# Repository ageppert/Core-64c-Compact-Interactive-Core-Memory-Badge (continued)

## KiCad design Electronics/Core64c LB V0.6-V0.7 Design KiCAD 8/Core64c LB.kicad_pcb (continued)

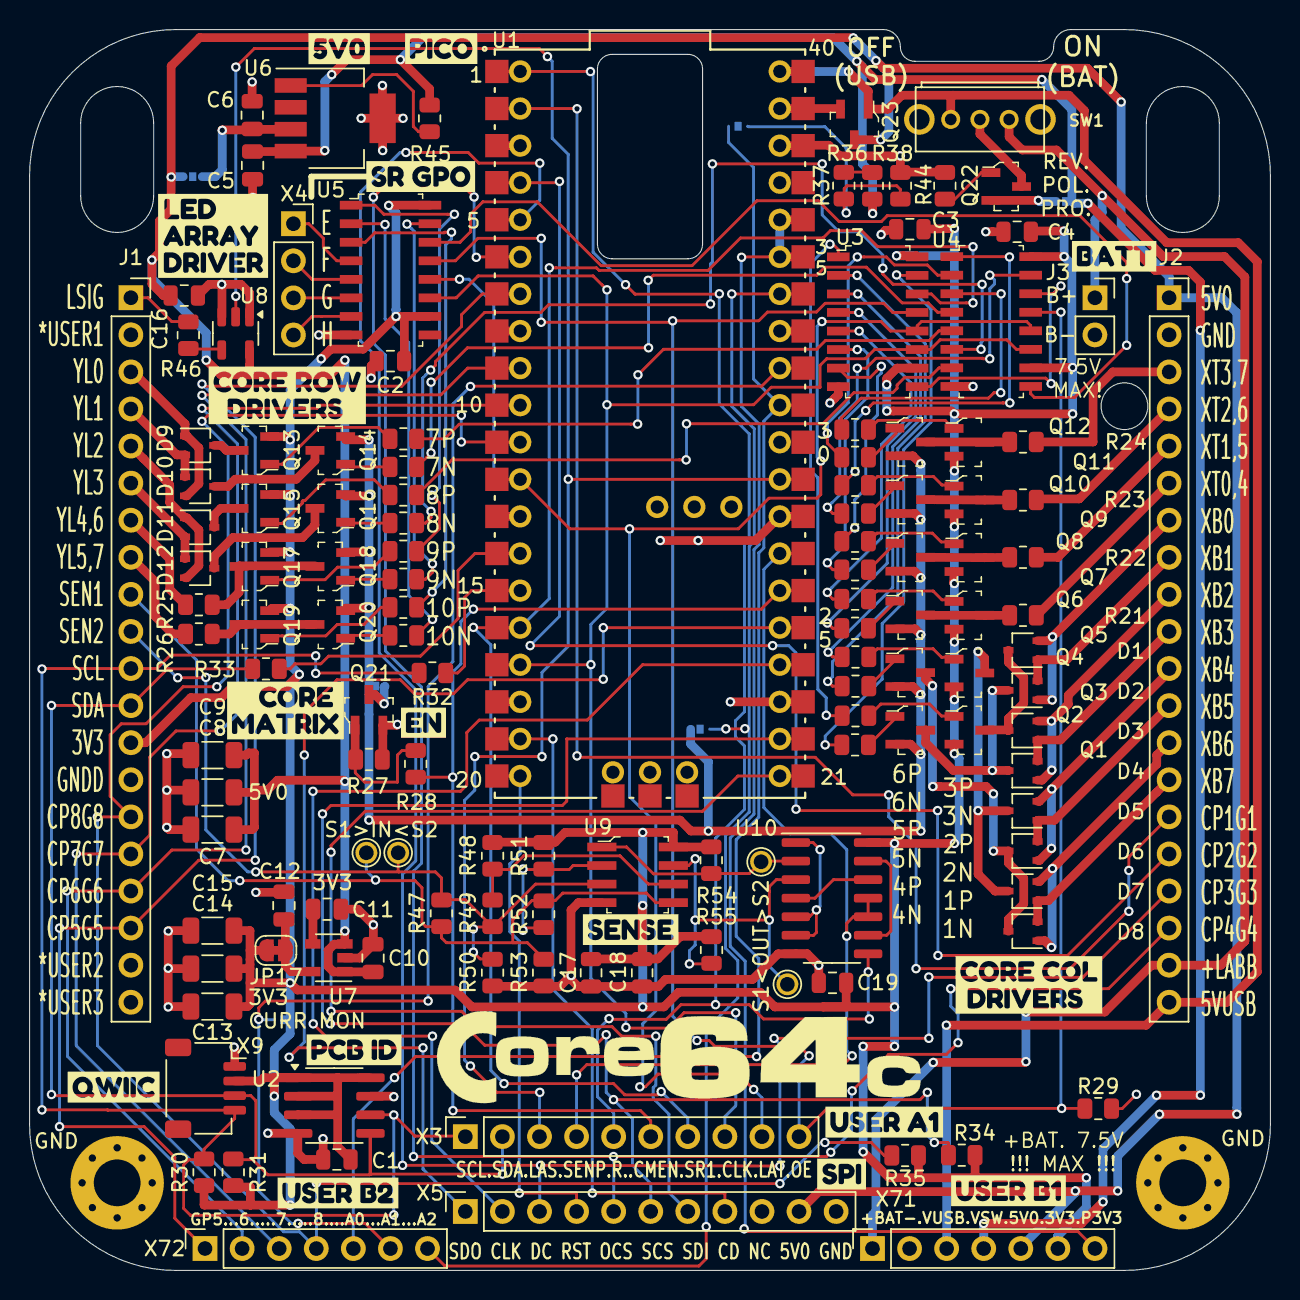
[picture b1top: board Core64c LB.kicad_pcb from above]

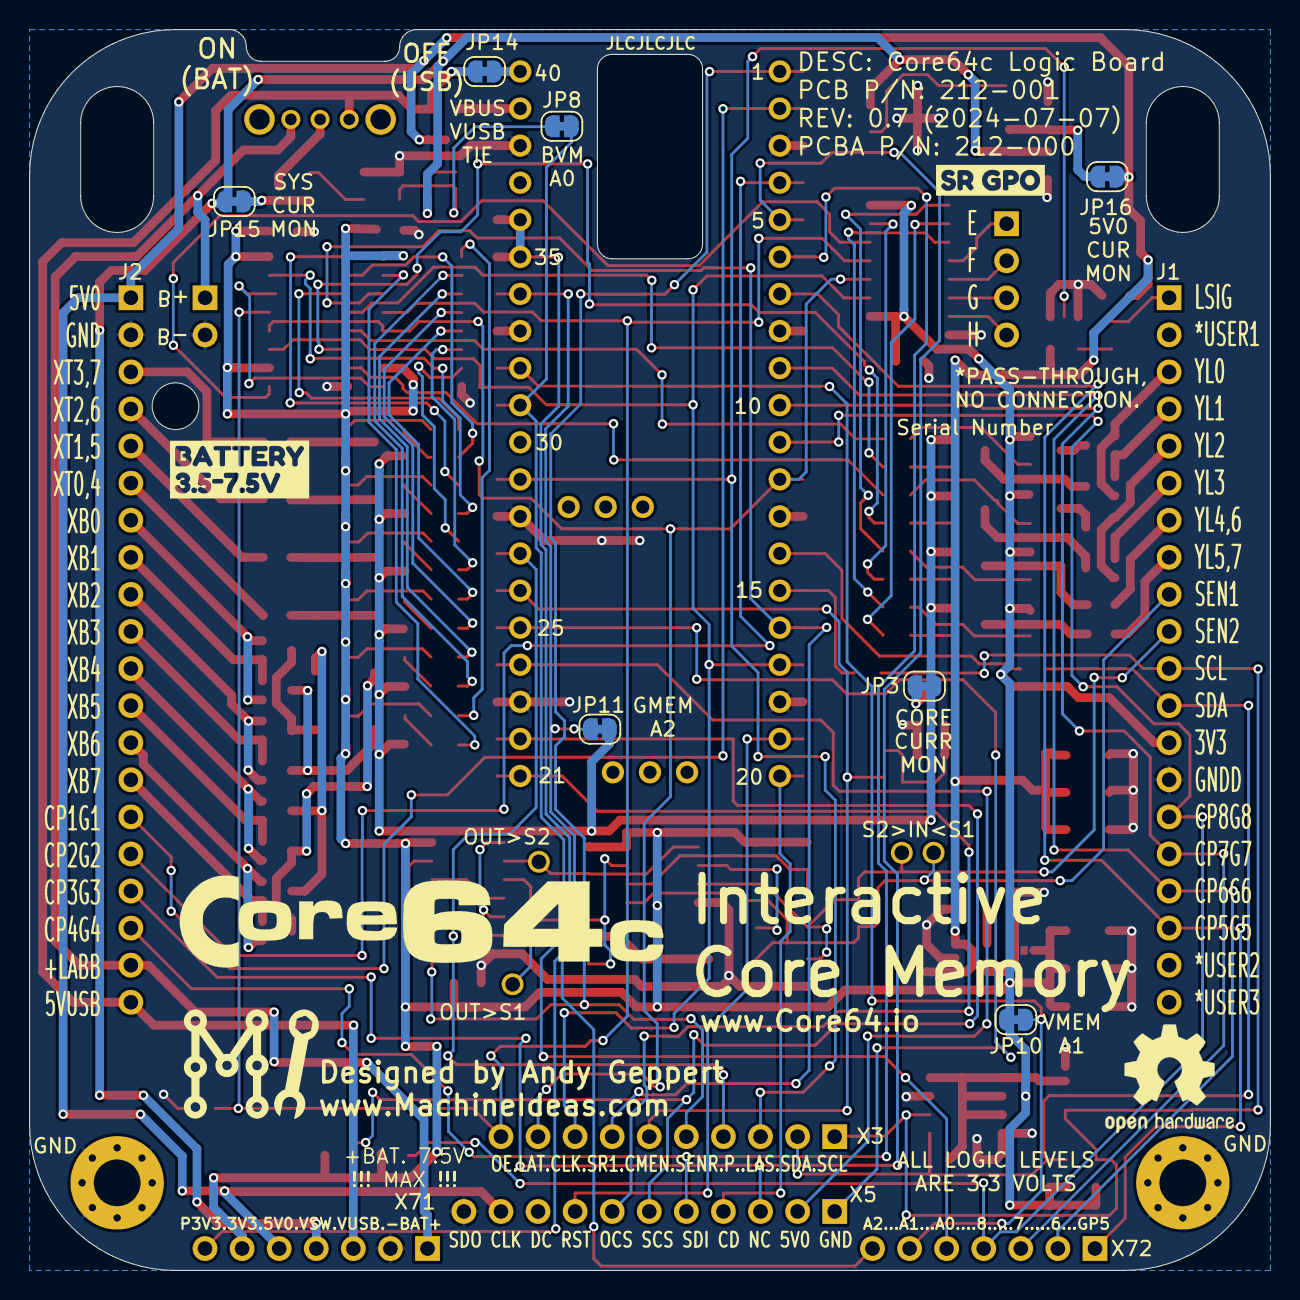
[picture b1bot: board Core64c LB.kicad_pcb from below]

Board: 2 copper layers, 85.0 x 85.0 mm, 161 parts (11 on the bottom side), 138 nets.

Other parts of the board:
L3#2: Logo_Open_Hardware_Small; OSHW-Logo2_9.8x8mm_SilkScreen
kibuzzard-668B4A9A: G***; kibuzzard-668B4A9A
kibuzzard-668B4AC0: G***; kibuzzard-668B4AC0
kibuzzard-668B4B17: G***; kibuzzard-668B4B17
kibuzzard-668B4C2C: G***; kibuzzard-668B4C2C
kibuzzard-668B4C14: G***; kibuzzard-668B4C14
kibuzzard-668B4C20: G***; kibuzzard-668B4C20
kibuzzard-668B4CFD: G***; kibuzzard-668B4CFD
kibuzzard-668B5F7C: G***; kibuzzard-668B5F7C
kibuzzard-668B48EA: G***; kibuzzard-668B48EA
kibuzzard-668B48F5: G***; kibuzzard-668B48F5
kibuzzard-668B48FD: G***; kibuzzard-668B48FD
kibuzzard-668B4889: G***; kibuzzard-668B4889
kibuzzard-668B4910: G***; kibuzzard-668B4910
kibuzzard-668B4919: G***; kibuzzard-668B4919
kibuzzard-668B4920: G***; kibuzzard-668B4920
kibuzzard-668B4929: G***; kibuzzard-668B4929
kibuzzard-668B4946: G***; kibuzzard-668B4946
kibuzzard-668B5072: G***; kibuzzard-668B5072

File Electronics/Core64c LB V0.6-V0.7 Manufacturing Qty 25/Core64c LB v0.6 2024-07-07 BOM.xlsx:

Comment | Designator | Footprint | LCSC Part Number | Substituted
0.1uF | C1, C2, C3, C4, C16, C17, C19 | Capacitor_SMD:C_0805_2012Metric | C28233
1uF | C5, C6, C10, C12 | Capacitor_SMD:C_0805_2012Metric | C28323
220uF | C7, C8, C9, C13, C14, C15 | Capacitor_SMD:C_1206_3216Metric | C412252
0.01uF | C11 | Capacitor_SMD:C_0805_2012Metric | C1710
10uF | C18 | Capacitor_SMD:C_0805_2012Metric | C17024
BAT54AW | D1, D3, D5, D7, D9, D11 | Package_TO_SOT_SMD:SOT-323_SC-70 | C78261
BAT54CW | D2, D4, D6, D8, D10, D12 | Package_TO_SOT_SMD:SOT-323_SC-70 | C83573 | C5240624
MMBT4403LT1G | Q1, Q3, Q5, Q7, Q9, Q11, Q13, Q15, Q17, Q19 | digikey-footprints:SOT-23-3 | C78864
MMBT4401LT1G | Q2, Q4, Q6, Q8, Q10, Q12, Q14, Q16, Q18, Q20 | digikey-footprints:SOT-23-3 | C31776
Q_NMOS_DGS_AO3400A | Q21 | digikey-footprints:SOT-23-3 | C20917
SL3401A | Q22, Q23 | digikey-footprints:SOT-23-3 | C350311
470 | R1, R2, R3, R4, R5, R6, R7, R8, R9, R10, R11, R12, R13, R14, R15, R16, R17, R18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 | Resistor_SMD:R_0805_2012Metric | C17710
8R2-1% | R21, R22, R23, R24, R25, R26 | Resistor_SMD:R_0805_2012Metric | C17830
10k | R27, R29, R34, R35, R36, R37, R38, R44, R45, R54, R55 | Resistor_SMD:R_0805_2012Metric | C17673 | This may have been 4.7K
1K2 | R30, R31 | Resistor_SMD:R_0805_2012Metric | C17379
68 | R32, R33 | Resistor_SMD:R_0805_2012Metric | C17802
1K5-1% | R47, R50, R53 | Resistor_SMD:R_0805_2012Metric | C4310
1K8-1% | R48, R51 | Resistor_SMD:R_0805_2012Metric | C17398
11-1% | R49, R52 | Resistor_SMD:R_0805_2012Metric | C17430
SK12D07L4B | SW1 | Switch_XKB_SK12D07VG4_SK12D07L4B:SK12D07VG4 | C480340
M24C02 | U2 | Package_SO:SOIC-8_3.9x4.9mm_P1.27mm | C7562
74HC595D | U3, U4, U5 | digikey-footprints:SOIC-16_W3.90mm | C5947
LP38693MP-5.0 | U6 | Package_TO_SOT_SMD:SOT-223-5 | C140294
SSP9193-33M5R | U7 | Package_TO_SOT_SMD:SOT-23-5 | C411022
SN74LV1T125DBVR | U8 | Package_TO_SOT_SMD:SOT-23-5 | C473338
LM393 | U9 | digikey-footprints:SOIC-8_W3.9mm | C7955
74HC02 | U10 | Package_SO:SOIC-14_3.9x8.7mm_P1.27mm | C350559
Conn_4_QWIIC | X9 | Connector_JST:JST_SH_SM04B-SRSS-TB_1x04-1MP_P1.00mm_Horizontal | C160404

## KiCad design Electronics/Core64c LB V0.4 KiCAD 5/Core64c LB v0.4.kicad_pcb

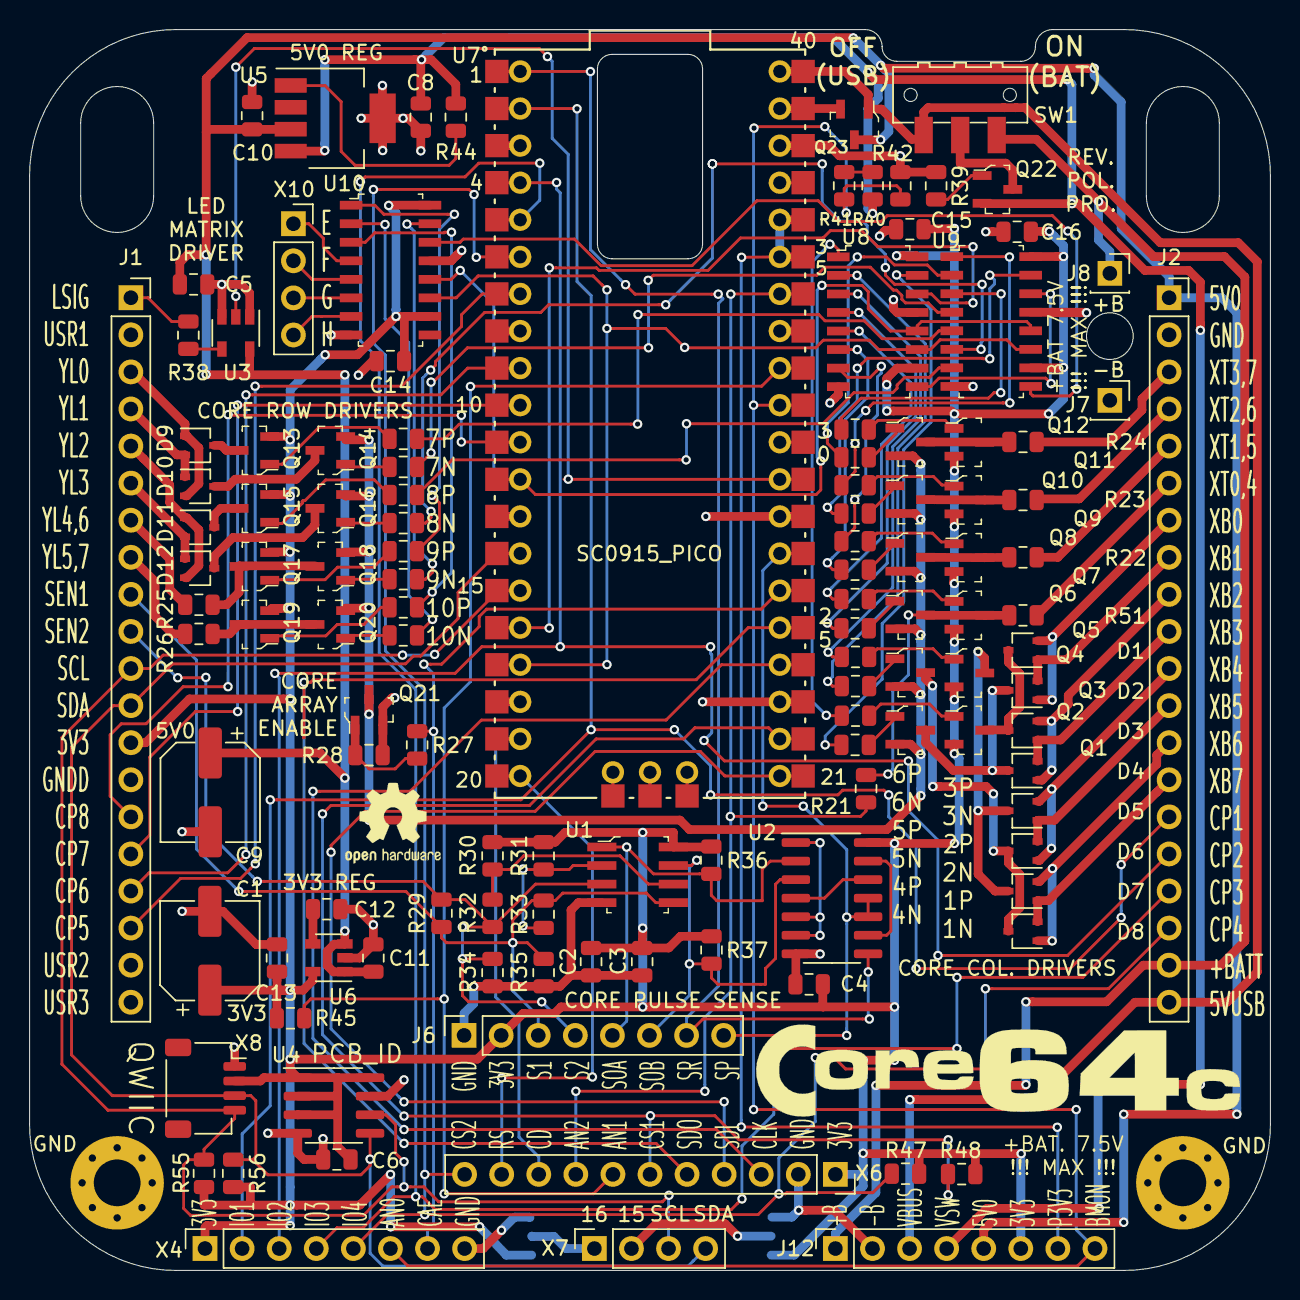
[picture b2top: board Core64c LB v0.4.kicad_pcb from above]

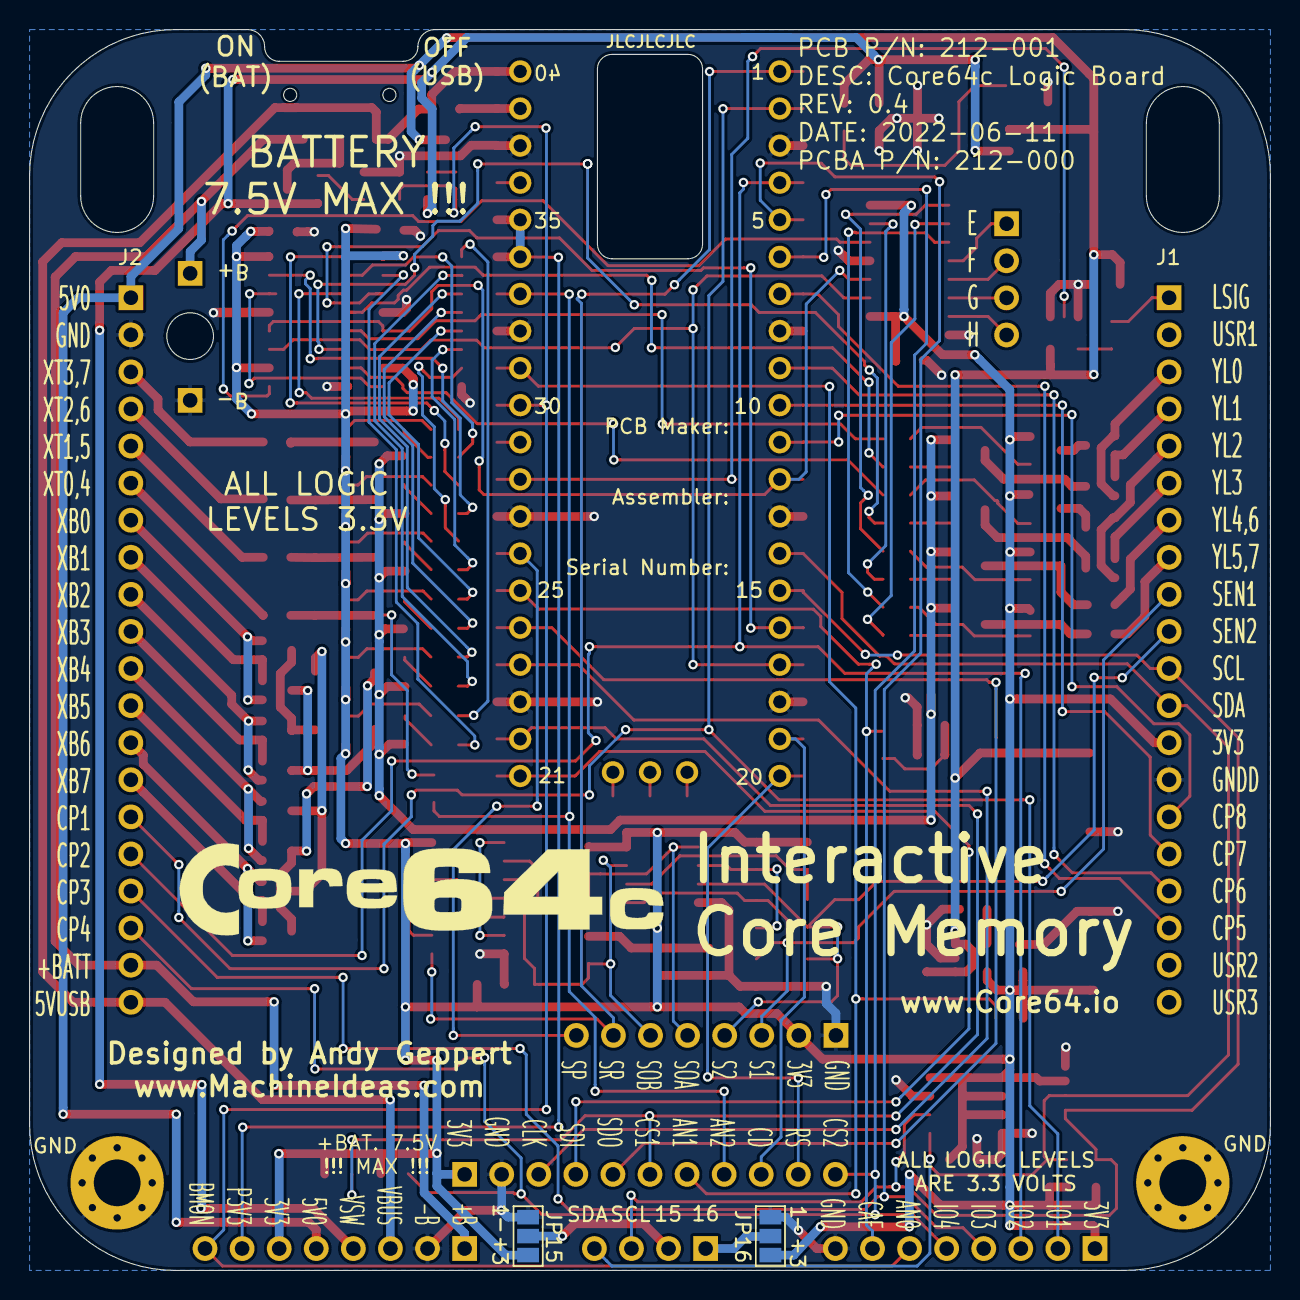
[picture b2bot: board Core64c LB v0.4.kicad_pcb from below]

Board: 2 copper layers, 85.0 x 85.0 mm, 128 parts (3 on the bottom side), 132 nets.

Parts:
C1, C9: 470uF; CP_Elec_6.3x7.7
C2, C4, C5, C6, C14, C15, C16: 0.1uF; C_0805_2012Metric
C3: 10uF; C_0805_2012Metric
C8, C10, C11, C13: 1uF; C_0805_2012Metric
C12: 0.01uF; C_0805_2012Metric
D1, D3, D5, D7, D9, D11: BAT54AW; SOT-323_SC-70
D2, D4, D6, D8, D10, D12: BAT54CW; SOT-323_SC-70
H1, H2: GND PAD; MountingHole_3.2mm_M3_Pad_Via
J1, J2: HDR100IMP40F-G-V-TH; PinSocket_1x20_P2.54mm_Vertical
J6: SENSE DEBUG; PinSocket_1x08_P2.54mm_Vertical
J7: ALT. BATT-; PinSocket_1x01_P2.54mm_Vertical
J8: ALT. BATT+; PinSocket_1x01_P2.54mm_Vertical
J12: Conn_01x08_Female; PinSocket_1x08_P2.54mm_Vertical
JP15, JP16: SolderJumper_3_Open; SolderJumper-3_P1.3mm_Open_Pad1.0x1.5mm_NumberLabels
L1, L2: Core_64c_Logo_7mm_tall; Core64c_Logo_7mm
L3: Logo_Open_Hardware_Small; OSHW-Logo2_7.3x6mm_SilkScreen
Q1, Q3, Q5, Q7, Q9, Q11, Q13, Q15, Q17, Q19: MMBT4403LT1G; SOT-23-3
Q2, Q4, Q6, Q8, Q10, Q12, Q14, Q16, Q18, Q20: MMBT4401LT1G; SOT-23-3
Q21: Q_NMOS_DGS_AO3400A; SOT-23-3
Q22, Q23: SL3401A; SOT-23-3
R1, R2, R3, R4, R5, R6, R7, R8, R9, R10, R11, R12, R13, R14, R15, R16, R17, R18, R19, R20, R27, R38: 470; R_0805_2012Metric
R21, R28, R39, R40, R41, R42, R44, R45: 10k; R_0805_2012Metric
R22, R23, R24, R25, R26, R51: 6R8-1%; R_0805_2012Metric
R29, R34, R35: 1K5-1%; R_0805_2012Metric
R30, R31: 1K8-1%; R_0805_2012Metric
R32, R33: 11-1%; R_0805_2012Metric
R36, R37, R55, R56: 1K2; R_0805_2012Metric
R47, R48: 10K; R_0805_2012Metric
SW1: JS102011SAQN; SW_SPDT_CK-JS102011SAQN_Core64_Recessed
U1: LM393; SOIC-8_W3.9mm
U2: 74HC02; SOIC-14_3.9x8.7mm_P1.27mm
U3: SN74LV1T125DBVR; SOT-23-5
U4: M24C02; SOIC-8_3.9x4.9mm_P1.27mm
U5: LP38693MP-5.0; SOT-223-5
U6: SGM2007-3.3XN5_TR; SOT-23-5
U7: SC0915_PICO; Pico_SC0915_THRUHOLE_CUTOUTS
U8, U9, U10: 74HC595D; SOIC-16_W3.90mm
X4: HEADER_8-PIN_0.1; PinSocket_1x08_P2.54mm_Vertical
X6: HEADER_11-PIN_0.1; PinSocket_1x11_P2.54mm_Vertical
X7, X10: HEADER_4-PIN_0.1; PinSocket_1x04_P2.54mm_Vertical
X8: QWIIC; JST_SH_SM04B-SRSS-TB_1x04-1MP_P1.00mm_Horizontal

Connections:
3V3: C1.1, C2.1, C3.1, C4.1, C6.1, C13.1, C14.1, C15.1, C16.1, J1.13, J6.2, J12.6, JP15.3, JP16.3, Q1.2, Q3.2, Q5.2, Q7.2, Q9.2, Q11.2, Q13.2, Q15.2, Q17.2, Q19.2, R30.1, R31.1, R36.1, R37.1, R45.2, R47.1, R48.1, R55.1, R56.1, U1.8, U2.14, U4.1, U4.2, U4.3, U4.8, U6.5, U8.10, U8.16, U9.10, U9.16, U10.10, U10.16, X4.1, X6.1, X8.2
3V3_MON: R45.1, U7.32, X6.7
5V0: C5.1, C9.1, C10.1, C11.1, J2.1, J12.5, Q23.3, U3.5, U5.3, U6.1, U6.3
+BATT: J2.19, J8.1, J12.1, SW1.1
+VSW: C8.1, J12.4, Q22.2, R40.2, R44.1, U5.4
-BATT: C1.2, C2.2, C3.2, C4.2, C5.2, C6.2, C8.2, C9.2, C10.2, C11.2, C12.2, C13.2, C14.2, C15.2, C16.2, H1.1, H2.1, J1.14, J2.2, J6.1, J7.1, J12.2, JP15.1, JP16.1, Q21.2, R28.1, R34.2, R35.2, R39.2, R42.2, U1.4, U2.7, U3.1, U3.3, U4.4, U4.7, U5.5, U6.2, U7.3, U7.8, U7.13, U7.18, U7.23, U7.28, U7.33, U7.38, U8.8, U8.13, U9.8, U9.13, U10.8, U10.13, X4.8, X6.2, X8.1
BAT_MON: J12.8, R41.1, R42.1, U7.31, X4.6
CORE_ARRAY_ENABLE: R27.2, U7.26, X4.7
CP1_EN: J2.15, U7.2, X4.2
CP2_EN: J2.16, U7.4, X4.3
CP3_EN: J2.17, U7.5, X4.4
CP4_EN: J2.18, R47.2, U7.6, X4.5, X6.11
CP5_EN: J1.18, U7.7
CP6_EN: J1.17, U7.9
CP7_EN: J1.16, U7.10
CP8_EN: J1.15, U7.11
GNDPWR: Q2.2, Q4.2, Q6.2, Q8.2, Q10.2, Q12.2, Q14.2, Q16.2, Q18.2, Q20.2, Q21.3
I2C_CLOCK: J1.11, R55.2, U4.6, U7.15, X7.3, X8.4
I2C_DATA: J1.12, R56.2, U4.5, U7.14, X7.4, X8.3
LED_MATRIX_3V3_SIG: U3.2, U7.29
LED_MATRIX_5V0_SIG: J1.1, R38.1
unnamed: C12.1, U6.4
unnamed: D1.3, D3.3, Q1.3
unnamed: D2.3, D4.3, Q2.3
unnamed: D5.3, D7.3, Q3.3
unnamed: D6.3, D8.3, Q4.3
unnamed: D9.3, Q13.3
unnamed: D10.3, Q14.3
unnamed: D11.3, Q15.3
unnamed: D12.3, Q16.3
unnamed: JP15.2, X7.2
unnamed: JP16.2, X7.1
unnamed: Q1.1, R1.1
unnamed: Q2.1, R2.1
unnamed: Q3.1, R3.1
unnamed: Q4.1, R4.1
unnamed: Q5.1, R5.1
unnamed: Q5.3, Q6.3, R21.1, R51.1
unnamed: Q6.1, R6.1
unnamed: Q7.1, R7.1
unnamed: Q7.3, Q8.3, R22.2
unnamed: Q8.1, R8.1
unnamed: Q9.1, R9.1
unnamed: Q10.1, R10.1
unnamed: Q9.3, Q10.3, R23.2
unnamed: Q11.1, R11.1
unnamed: Q11.3, Q12.3, R24.2
unnamed: Q12.1, R12.1
unnamed: Q13.1, R13.1
unnamed: Q14.1, R14.1
unnamed: Q15.1, R15.1
unnamed: Q16.1, R16.1
unnamed: Q17.1, R17.1
unnamed: Q17.3, Q18.3, R25.2
unnamed: Q18.1, R18.1
unnamed: Q19.1, R19.1
unnamed: Q19.3, Q20.3, R26.2
unnamed: Q20.1, R20.1
unnamed: Q21.1, R27.1, R28.2
unnamed: Q22.1, R39.1
unnamed: Q22.3, SW1.2
unnamed: R30.2, R32.1, U1.6
unnamed: R31.2, R33.1, U1.2
unnamed: R38.2, U3.4
unnamed: R40.1, R41.2
unnamed: R44.2, U5.1
unnamed: U2.1, U2.5, U2.6
unnamed: U2.4, U2.12
unnamed: U2.9, U2.13
unnamed: U8.9, U9.14
unnamed: U10.4, X10.1
unnamed: U10.5, X10.2
unnamed: U10.6, X10.3
unnamed: U10.7, X10.4
unnamed: U9.9, U10.14
PICO_3V3OUT: J12.7, U7.35, U7.36
PICO_VBUS: J2.20, J12.3, Q23.1, SW1.3, U7.40
PICO_VSYS: Q23.2, U7.39
Q1N: R2.2, U8.15
Q1P: R1.2, U8.1
Q2N: R4.2, U8.2
Q2P: R3.2, U8.3
Q3N: R6.2, U8.4
Q3P: R5.2, U8.5
Q4N: R8.2, U8.6
Q4P: R7.2, U8.7
Q5N: R10.2, U9.15
Q5P: R9.2, U9.1
Q6N: R12.2, U9.2
Q6P: R11.2, U9.3
Q7N: R14.2, U9.4
Q7P: R13.2, U9.5
Q8N: R16.2, U9.6
Q8P: R15.2, U9.7
Q9N: R18.2, U10.15
Q9P: R17.2, U10.1
Q10N: R20.2, U10.2
Q10P: R19.2, U10.3
SENSE1: J1.9, J6.3, R29.1, R33.2, R35.1, U1.5
SENSE2: J1.10, J6.4, R29.2, R32.2, R34.1, U1.3
SENSE_OUT_A: J6.5, R36.2, U1.1, U2.2
SENSE_OUT_B: J6.6, R37.2, U1.7, U2.3
SENSE_PULSE: J6.8, U2.10, U2.11, U7.27
SENSE_RESET: J6.7, U2.8, U7.1
SPARE_ADC2: R21.2, U7.34, X6.8
SPI_CD: U7.19, X6.9
SPI_CLK: U7.24, X6.3
SPI_CS1: R48.2, U7.22, X6.6
SPI_RESET: U7.20, X6.10
SPI_SDI: U7.21, X6.4
SPI_SDO: U7.25, X6.5
SR_CLK: U7.17, U8.11, U9.11, U10.11
SR_LAT: U7.12, U8.12, U9.12, U10.12
SR_SER: U7.16, U8.14
XB0: D1.2, D2.1, J2.7
XB1: D1.1, D2.2, J2.8
XB2: D3.2, D4.1, J2.9
XB3: D3.1, D4.2, J2.10
XB4: D5.2, D6.1, J2.11
XB5: D5.1, D6.2, J2.12
XB6: D7.2, D8.1, J2.13
XB7: D7.1, D8.2, J2.14
XT0,4: J2.6, R51.2
XT1,5: J2.5, R22.1
XT2,6: J2.4, R23.1
XT3,7: J2.3, R24.1
YL0: D9.1, D10.2, J1.3
YL1: D9.2, D10.1, J1.4
YL2: D11.1, D12.2, J1.5
YL3: D11.2, D12.1, J1.6
YL4: J1.7, R25.1
YL5: J1.8, R26.1

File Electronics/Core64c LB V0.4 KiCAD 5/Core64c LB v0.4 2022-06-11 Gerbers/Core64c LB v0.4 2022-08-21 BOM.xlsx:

Comment | Designator | Footprint | LCSC Part Number
10uF | C3 | Capacitor_SMD:C_0805_2012Metric | C17024
470uF | C1, C9 | Capacitor_SMD:CP_Elec_6.3x7.7 | C335982
0.01uF | C12 | Capacitor_SMD:C_0805_2012Metric | C16834
1uF | C8, C10, C11, C13 | Capacitor_SMD:C_0805_2012Metric | C16834
0.1uF | C2, C4, C5, C6, C14, C15, C16 | Capacitor_SMD:C_0805_2012Metric | C28233
BAT54AW | D1, D3, D5, D7, D9, D11 | Package_TO_SOT_SMD:SOT-323_SC-70 | C78261
BAT54CW | D2, D4, D6, D8, D10, D12 | Package_TO_SOT_SMD:SOT-323_SC-70 | C83573
MMBT4403LT1G | Q1, Q3, Q5, Q7, Q9, Q11, Q13, Q15, Q17, Q19 | Digikey:SOT-23-3 | C78864
MMBT4401LT1G | Q2, Q4, Q6, Q8, Q10, Q12, Q14, Q16, Q18, Q20 | Digikey:SOT-23-3 | C31776
Q_NMOS_DGS_AO3400A | Q21 | Digikey:SOT-23-3 | C20917
SL3401A | Q22, Q23 | Digikey:SOT-23-3 | C350311
1K8-1% | R30, R31 | Resistor_SMD:R_0805_2012Metric | C17398
11-1% | R32, R33 | Resistor_SMD:R_0805_2012Metric | C17430
1K5-1% | R29, R34, R35 | Resistor_SMD:R_0805_2012Metric | C4310
1K2 | R36, R37, R55, R56 | Resistor_SMD:R_0805_2012Metric | C17379
470 | R1, R2, R3, R4, R5, R6, R7, R8, R9, R10, R11, R12, R13, R14, R15, R16, R17, R18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 | Resistor_SMD:R_0805_2012Metric | C17710
10k | R21, R28, R39, R40, R41, R42, R44, R45 | Resistor_SMD:R_0805_2012Metric | C17414
6R8-1% | R22, R23, R24, R25, R26, R51 | Resistor_SMD:R_0805_2012Metric | C17774
JS102011SAQN | SW1 | Button_Switch_SMD:SW_SPDT_CK-JS102011SAQN_Core64_Recessed | C221660
LM393 | U1 | Digikey:SOIC-8_W3.9mm | C7955
74HC02 | U2 | Package_SO:SOIC-14_3.9x8.7mm_P1.27mm | C350559
SN74LV1T125DBVR | U3 | Package_TO_SOT_SMD:SOT-23-5 | C473338
M24C02 | U4 | Package_SO:SOIC-8_3.9x4.9mm_P1.27mm | C7562
LP38693MP-5.0 | U5 | Package_TO_SOT_SMD:SOT-223-5 | C140294
SSP9193-33M5R | U6 | Package_TO_SOT_SMD:SOT-23-5 | C411022 | Replaced with part that is in stock now.
74HC595D | U8, U9, U10 | Digikey:SOIC-16_W3.90mm | C5947
QWIIC | X8 | Connector_JST:JST_SH_SM04B-SRSS-TB_1x04-1MP_P1.00mm_Horizontal | C160404 | INVENTORY SHORTAGE

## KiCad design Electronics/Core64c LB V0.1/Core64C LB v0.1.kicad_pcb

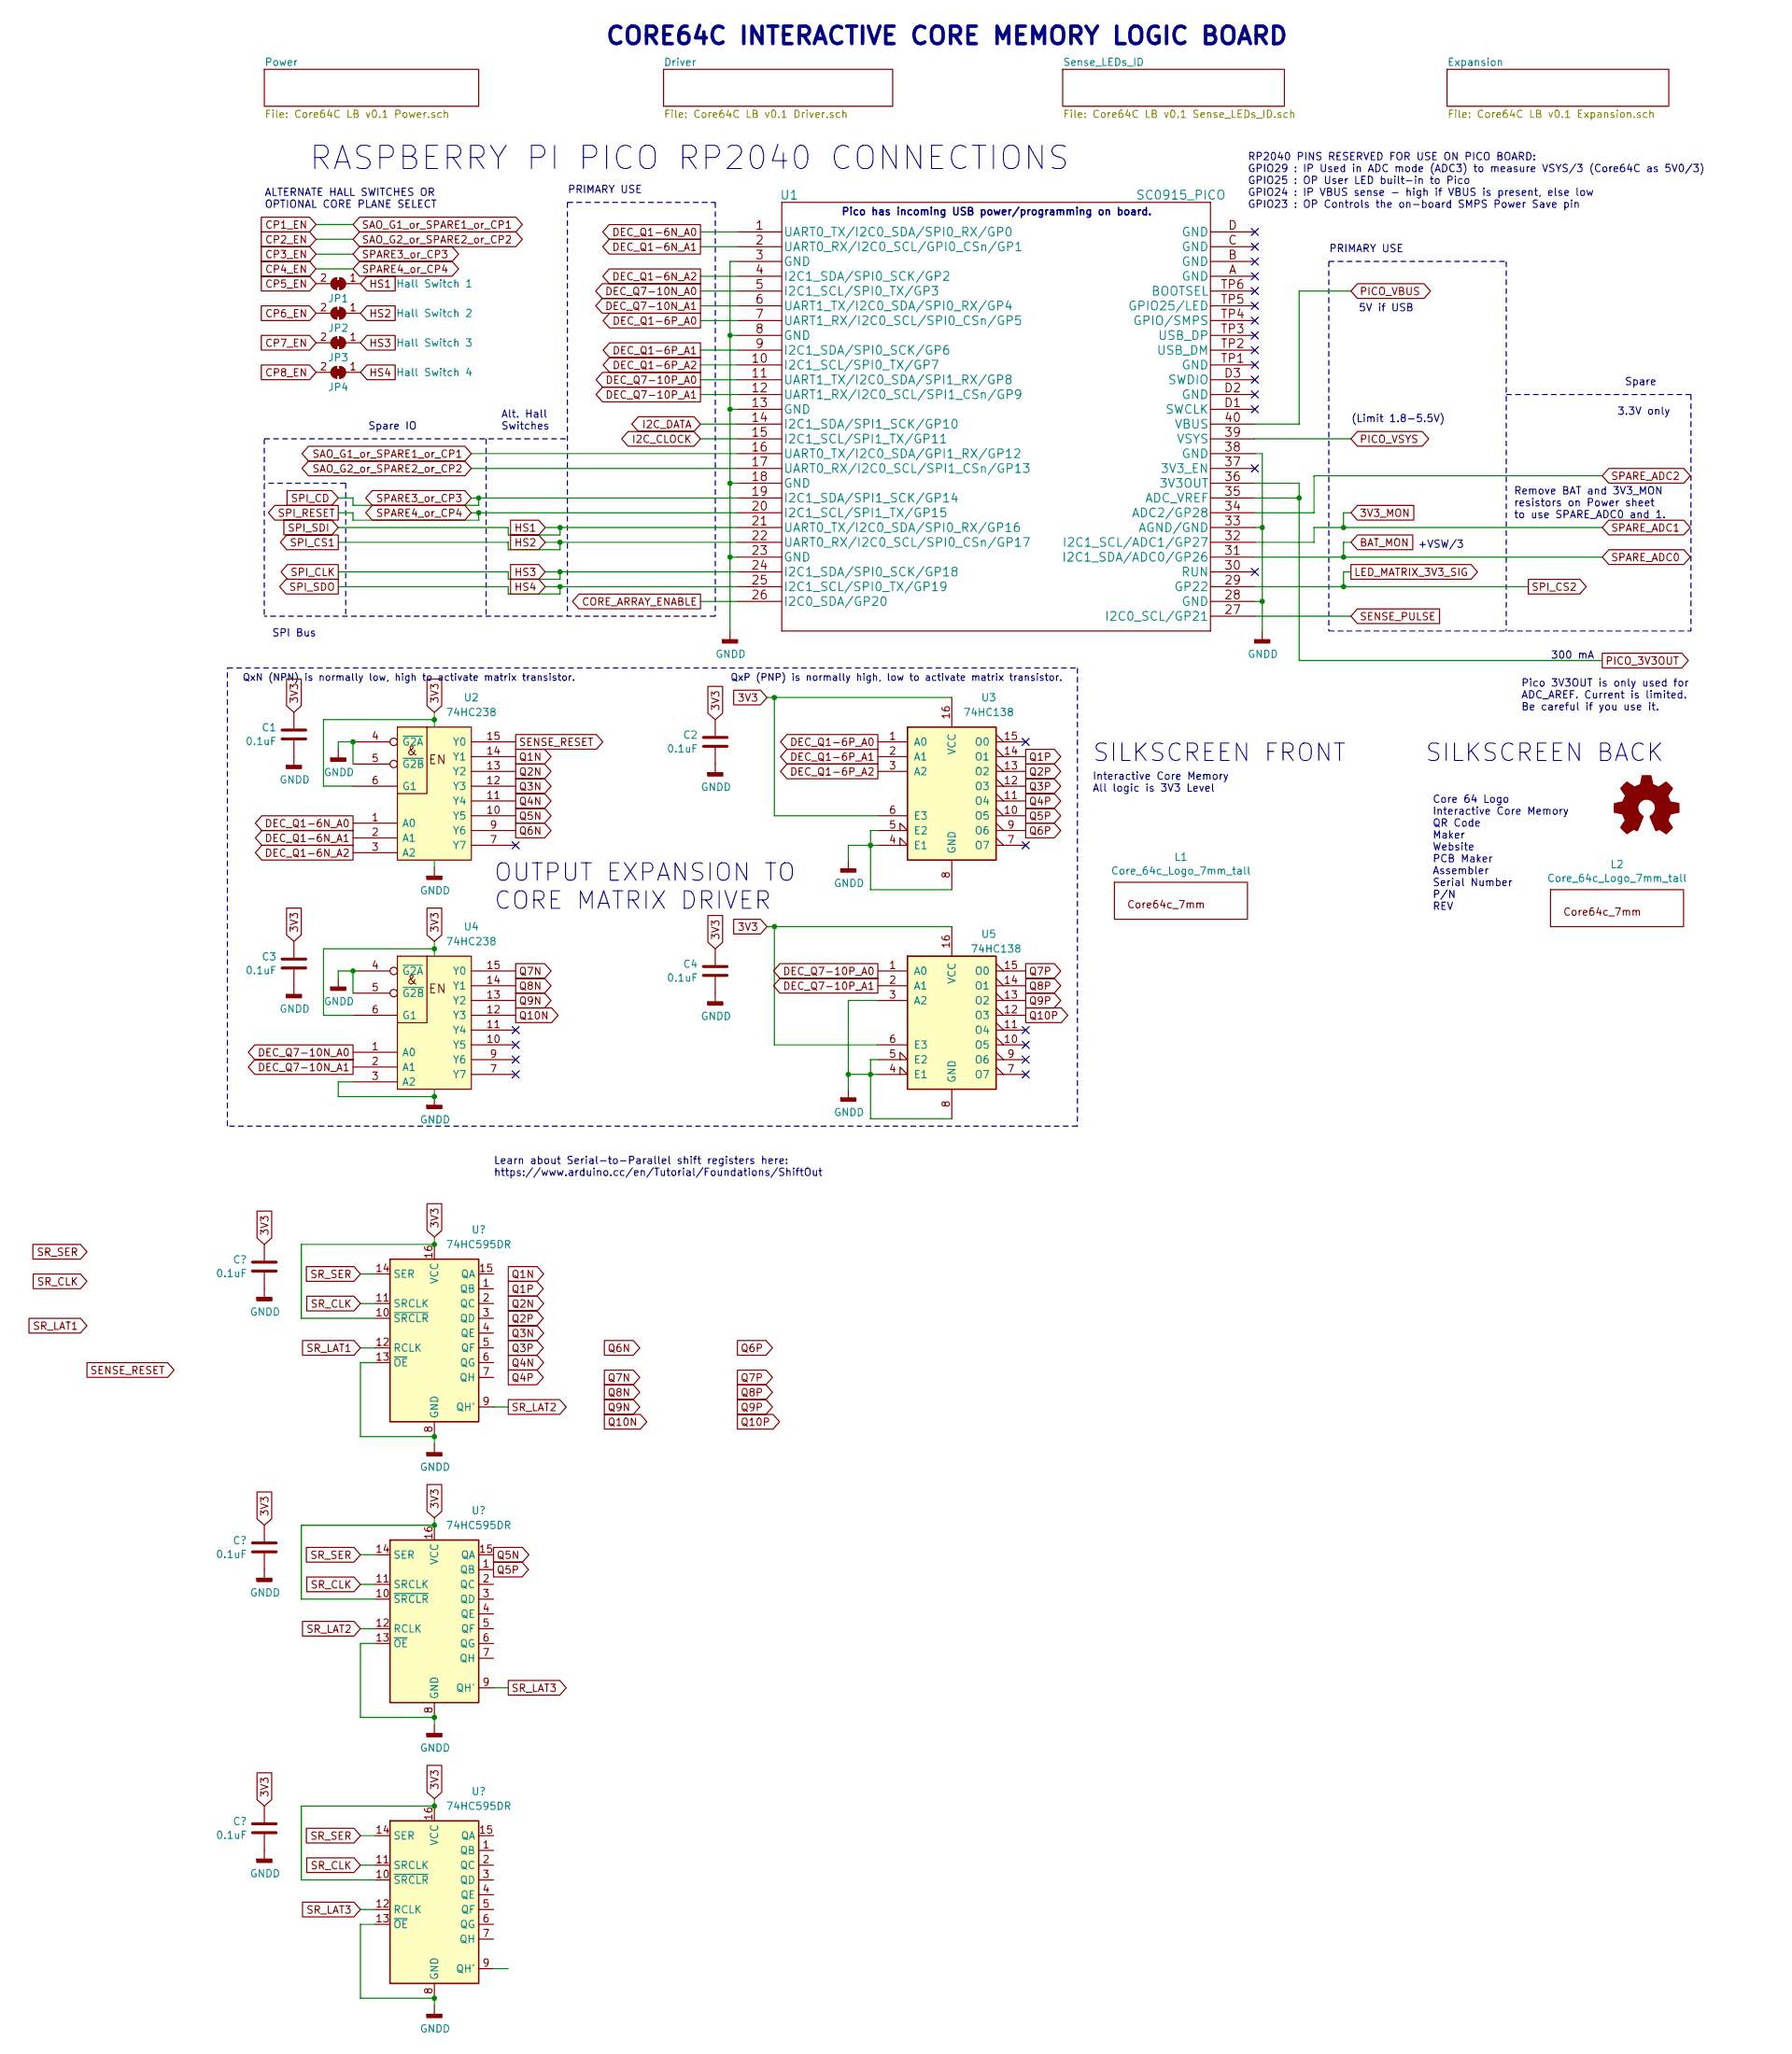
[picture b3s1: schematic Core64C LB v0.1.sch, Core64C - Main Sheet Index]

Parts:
C1, C2, C3, C4: 0.1uF; C_0805_2012Metric
JP1: Hall Switch 1; SolderJumper-2_P1.3mm_Bridged_RoundedPad1.0x1.5mm
JP2: Hall Switch 2; SolderJumper-2_P1.3mm_Bridged_RoundedPad1.0x1.5mm
JP3: Hall Switch 3; SolderJumper-2_P1.3mm_Bridged_RoundedPad1.0x1.5mm
JP4: Hall Switch 4; SolderJumper-2_P1.3mm_Bridged_RoundedPad1.0x1.5mm
L1, L2: Core_64c_Logo_7mm_tall; Core64c_Logo_7mm
L3: Logo_Open_Hardware_Small; OSHW-Logo2_7.3x6mm_SilkScreen
U1: SC0915_PICO; Pico_SC0915_THRUHOLE_CUTOUTS
U2, U4: 74HC238; SOIC-16_W3.90mm
U3, U5: 74HC138; SOIC-16_W3.90mm

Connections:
3V3: C1.1, C2.1, C3.1, C4.1, U2.6 (G1), U2.16 (VCC), U3.6 (_), U3.16 (VCC), U4.6 (G1), U4.16 (VCC), U5.6 (E3), U5.16 (VCC); also elsewhere on the board
3V3_MON: U1.32 (I2C1_SCL/ADC1/GP27); also elsewhere on the board
-BATT: C1.2, C2.2, C3.2, C4.2, U1.3 (GND), U1.8 (GND), U1.13 (GND), U1.18 (GND), U1.23 (GND), U1.28 (GND), U1.33 (AGND/GND), U1.38 (GND), U2.4 (~G2A), U2.5 (~G2B), U2.8 (GND), U3.4 (V-), U3.5 (+), U3.8 (V+), U4.3 (A2), U4.4 (~G2A), U4.5 (~G2B), U4.8 (GND), U5.3 (A2), U5.4 (E1), U5.5 (E2), U5.8 (GND); also elsewhere on the board
BAT_MON: U1.31 (I2C1_SDA/ADC0/GP26); also elsewhere on the board
CORE_ARRAY_ENABLE: U1.26 (I2C0_SDA/GP20); also elsewhere on the board
CP1_EN: U1.16 (UART0_TX/I2C0_SDA/GPI1_RX/GP12); also elsewhere on the board
CP2_EN: U1.17 (UART0_RX/I2C0_SCL/SPI1_CSn/GP13); also elsewhere on the board
CP3_EN: U1.19 (I2C1_SDA/SPI1_SCK/GP14); also elsewhere on the board
CP4_EN: U1.20 (I2C1_SCL/SPI1_TX/GP15); also elsewhere on the board
CP5_EN: JP1.2 (B); also elsewhere on the board
CP6_EN: JP2.2 (B); also elsewhere on the board
CP7_EN: JP3.2 (B); also elsewhere on the board
CP8_EN: JP4.2 (B); also elsewhere on the board
DEC_Q1-6N_A0: U1.1 (UART0_TX/I2C0_SDA/SPI0_RX/GP0), U2.1 (A0)
DEC_Q1-6N_A1: U1.2 (UART0_RX/I2C0_SCL/GPI0_CSn/GP1), U2.2 (A1)
DEC_Q1-6N_A2: U1.4 (I2C1_SDA/SPI0_SCK/GP2), U2.3 (A2)
DEC_Q7-10N_A0: U1.5 (I2C1_SCL/SPI0_TX/GP3), U4.1 (A0)
DEC_Q7-10N_A1: U1.6 (UART1_TX/I2C0_SDA/SPI0_RX/GP4), U4.2 (A1)
DEC_Q7-10P_A0: U1.11 (UART1_TX/I2C0_SDA/SPI1_RX/GP8), U5.1 (A0)
DEC_Q7-10P_A1: U1.12 (UART1_RX/I2C0_SCL/SPI1_CSn/GP9), U5.2 (A1)
HS1: JP1.1 (A), U1.21 (UART0_TX/I2C0_SDA/SPI0_RX/GP16); also elsewhere on the board
HS2: JP2.1 (A), U1.22 (UART0_RX/I2C0_SCL/SPI0_CSn/GP17); also elsewhere on the board
HS3: JP3.1 (A), U1.24 (I2C1_SDA/SPI0_SCK/GP18); also elsewhere on the board
HS4: JP4.1 (A), U1.25 (I2C1_SCL/SPI0_TX/GP19); also elsewhere on the board
I2C_CLOCK: U1.15 (I2C1_SCL/SPI1_TX/GP11); also elsewhere on the board
I2C_DATA: U1.14 (I2C1_SDA/SPI1_SCK/GP10); also elsewhere on the board
LED_MATRIX_3V3_SIG: U1.29 (GP22); also elsewhere on the board
PICO_3V3OUT: U1.35 (ADC_VREF), U1.36 (3V3OUT); also elsewhere on the board
PICO_VBUS: U1.40 (VBUS); also elsewhere on the board
PICO_VSYS: U1.39 (VSYS); also elsewhere on the board
Q1N: U2.14 (Y1); also elsewhere on the board
Q1P: U3.14 (O1); also elsewhere on the board
Q2N: U2.13 (Y2); also elsewhere on the board
Q2P: U3.13 (O2); also elsewhere on the board
Q3N: U2.12 (Y3); also elsewhere on the board
Q3P: U3.12 (O3); also elsewhere on the board
Q4N: U2.11 (Y4); also elsewhere on the board
Q4P: U3.11 (O4); also elsewhere on the board
Q5N: U2.10 (Y5); also elsewhere on the board
Q5P: U3.10 (O5); also elsewhere on the board
Q6N: U2.9 (Y6); also elsewhere on the board
Q6P: U3.9 (O6); also elsewhere on the board
Q7N: U4.15 (Y0); also elsewhere on the board
Q7P: U5.15 (O0); also elsewhere on the board
Q8N: U4.14 (Y1); also elsewhere on the board
Q8P: U5.14 (O1); also elsewhere on the board
Q9N: U4.13 (Y2); also elsewhere on the board
Q9P: U5.13 (O2); also elsewhere on the board
Q10N: U4.12 (Y3); also elsewhere on the board
Q10P: U5.12 (O3); also elsewhere on the board
SENSE_PULSE: U1.27 (I2C0_SCL/GP21); also elsewhere on the board
SENSE_RESET: U2.15 (Y0); also elsewhere on the board
SPARE_ADC2: U1.34 (ADC2/GP28); also elsewhere on the board

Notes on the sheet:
CORE64C INTERACTIVE CORE MEMORY LOGIC BOARD
+VSW/3
Pico has incoming USB power/programming on board.
RASPBERRY PI PICO RP2040 CONNECTIONS
Pico 3V3OUT is only used for ADC_AREF. Current is limited. Be careful if you use it.
PRIMARY USE
SILKSCREEN BACK
SILKSCREEN FRONT
Core 64 Logo Interactive Core Memory QR Code Maker Website PCB Maker Assembler Serial Number P/N REV
Interactive Core Memory All logic is 3V3 Level
Spare
Spare IO
SPI Bus
QxP (PNP) is normally high, low to activate matrix transistor.
OUTPUT EXPANSION TO CORE MATRIX DRIVER
RP2040 PINS RESERVED FOR USE ON PICO BOARD: GPIO29 : IP Used in ADC mode (ADC3) to measure VSYS/3 (Core64C as 5V0/3) GPIO25 : OP User LED built-in to Pico GPIO24 : IP VBUS sense - high if VBUS is present, else low GPIO23 : OP Controls the on-board SMPS Power Save pin
Alt. Hall Switches
3.3V only
300 mA
5V if USB
(Limit 1.8-5.5V)
QxN (NPN) is normally low, high to activate matrix transistor.
Remove BAT and 3V3_MON resistors on Power sheet to use SPARE_ADC0 and 1.
ALTERNATE HALL SWITCHES OR OPTIONAL CORE PLANE SELECT
Learn about Serial-to-Parallel shift registers here: https://www.arduino.cc/en/Tutorial/Foundations/ShiftOut
